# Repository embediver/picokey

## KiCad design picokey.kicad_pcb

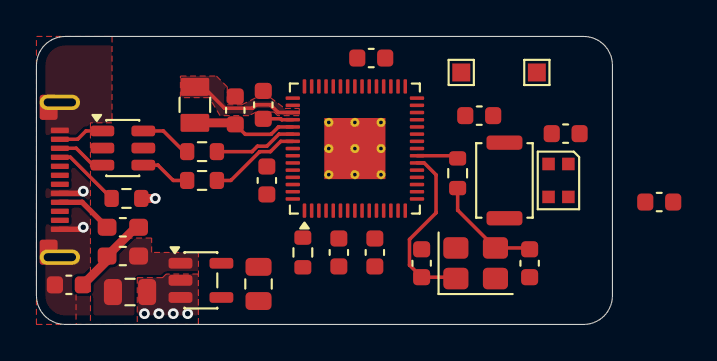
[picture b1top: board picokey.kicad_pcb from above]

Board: 2 copper layers, 32.0 x 16.0 mm, 31 parts (0 on the bottom side), 22 nets.

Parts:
C1: 10u/10V; C_0805_2012Metric
C2, C3, C4: 4u7/6.3V/X5R; C_0603_1608Metric
C5, C6, C7, C8, C9, C10: 100n; C_0603_1608Metric
C27: 680n; C_0603_1608Metric
C29, C30: 20p/25V/C0G; C_0603_1608Metric
C49: 1u; C_0805_2012Metric
D1: WS2812B; LED_WS2812B-2020_PLCC4_2.0x2.0mm
L1: 3u3; L_0806
L2, L3: L; L_0603_1608Metric_Pad1.05x0.95mm_HandSolder
P1: USB_C_Plug_USB2.0; USB_C_Plug_XKB_U261-121N-4BS2S
R1, R2: 27R; R_0603_1608Metric
R3: 5k1; R_0603_1608Metric
R4, R32: 1k; R_0603_1608Metric
SW1: Function; SW_Push_SPST_NO_Alps_SKRK
TP1: SWCLK; TestPoint_Pad_1.0x1.0mm
TP2: SWDIO; TestPoint_Pad_1.0x1.0mm
U1: RP2354A; QFN-60-1EP_7x7mm_P0.4mm_EP3.4x3.4mm_ThermalVias
U10: WE-TVS-82400102; SOT-23-6
U14: TPS76933; SOT-23-5
Y1: 12MHz SMD3225-4P; Crystal_SMD_3225-4Pin_3.2x2.5mm

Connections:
+1V1: C2.1, C4.1, C5.1, L1.1, U1.6 (DVDD), U1.23 (DVDD), U1.39 (DVDD), U1.50 (VREG_FB)
+3V3: C1.1, C3.1, C6.1, C7.1, C8.1, C9.1, U1.1 (IOVDD), U1.11 (IOVDD), U1.20 (IOVDD), U1.26 (RUN), U1.30 (IOVDD), U1.38 (IOVDD), U1.45 (IOVDD), U1.49 (VREG_VIN), U1.53 (USB_OTP_VDD), U1.54 (QSPI_IOVDD), U14.5 (OUT)
+5V: C10.1, C49.1, D1.1 (VDD), L3.2, U14.1 (IN)
/BUTTON: R4.2, U1.60 (QSPI_SS)
/LED_DAT: D1.4 (DIN), U1.5 (GPIO3)
/SWCLK: TP1.1, U1.24 (SWCLK)
/SWDIO: TP2.1, U1.25 (SWDIO)
/USB_DM: P1.A7 (D-), U10.1
/USB_DM_ESD: R1.1, U10.6
/USB_DM_RP: R1.2, U1.51 (USB_DM)
/USB_DP: P1.A6 (D+), U10.3
/USB_DP_ESD: R2.1, U10.4
/USB_DP_RP: R2.2, U1.52 (USB_DP)
/VBUS: L2.1, P1.A4 (VBUS), P1.B9 (VBUS), U10.5
/VBus_{2}: C27.1, L2.2, L3.1
/VREG_LX: L1.2, U1.48 (VREG_LX)
/XIN: C29.1, U1.21 (XIN), Y1.1
/XOUT: R32.2, U1.22 (XOUT)
/XTAL: C30.1, R32.1, Y1.3
GND: C1.2, C2.2, C3.2, C4.2, C5.2, C6.2, C7.2, C8.2, C9.2, C10.2, C27.2, C29.2, C30.2, C49.2, D1.3 (VSS), P1.A1 (GND), P1.A12 (GND), P1.B12 (GND), P1.S1 (SHIELD), R3.2, SW1.1, U1.47 (VREG_PGND), U1.61 (GND), U10.2, U14.2 (GND), U14.3 (~EN), Y1.2, Y1.4
unnamed: P1.A5 (CC), R3.1
unnamed: R4.1, SW1.2

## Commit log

2025-11-22 First layout
